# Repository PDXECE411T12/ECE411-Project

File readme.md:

# ECE 411 Team 12 
## RFID Smart Lock

### Fall 2020
### Authors: Miles Breslin, Miguel Higgins Moy, John Sharpe, Noah Page

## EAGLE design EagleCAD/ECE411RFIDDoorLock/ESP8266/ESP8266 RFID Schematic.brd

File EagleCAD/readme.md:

Schematic forked from Adafruit's wonderful ESP8266 Huzzah PCB

<https://github.com/PDXECE411T12/ECE411-RFID-Lock-Eagle>

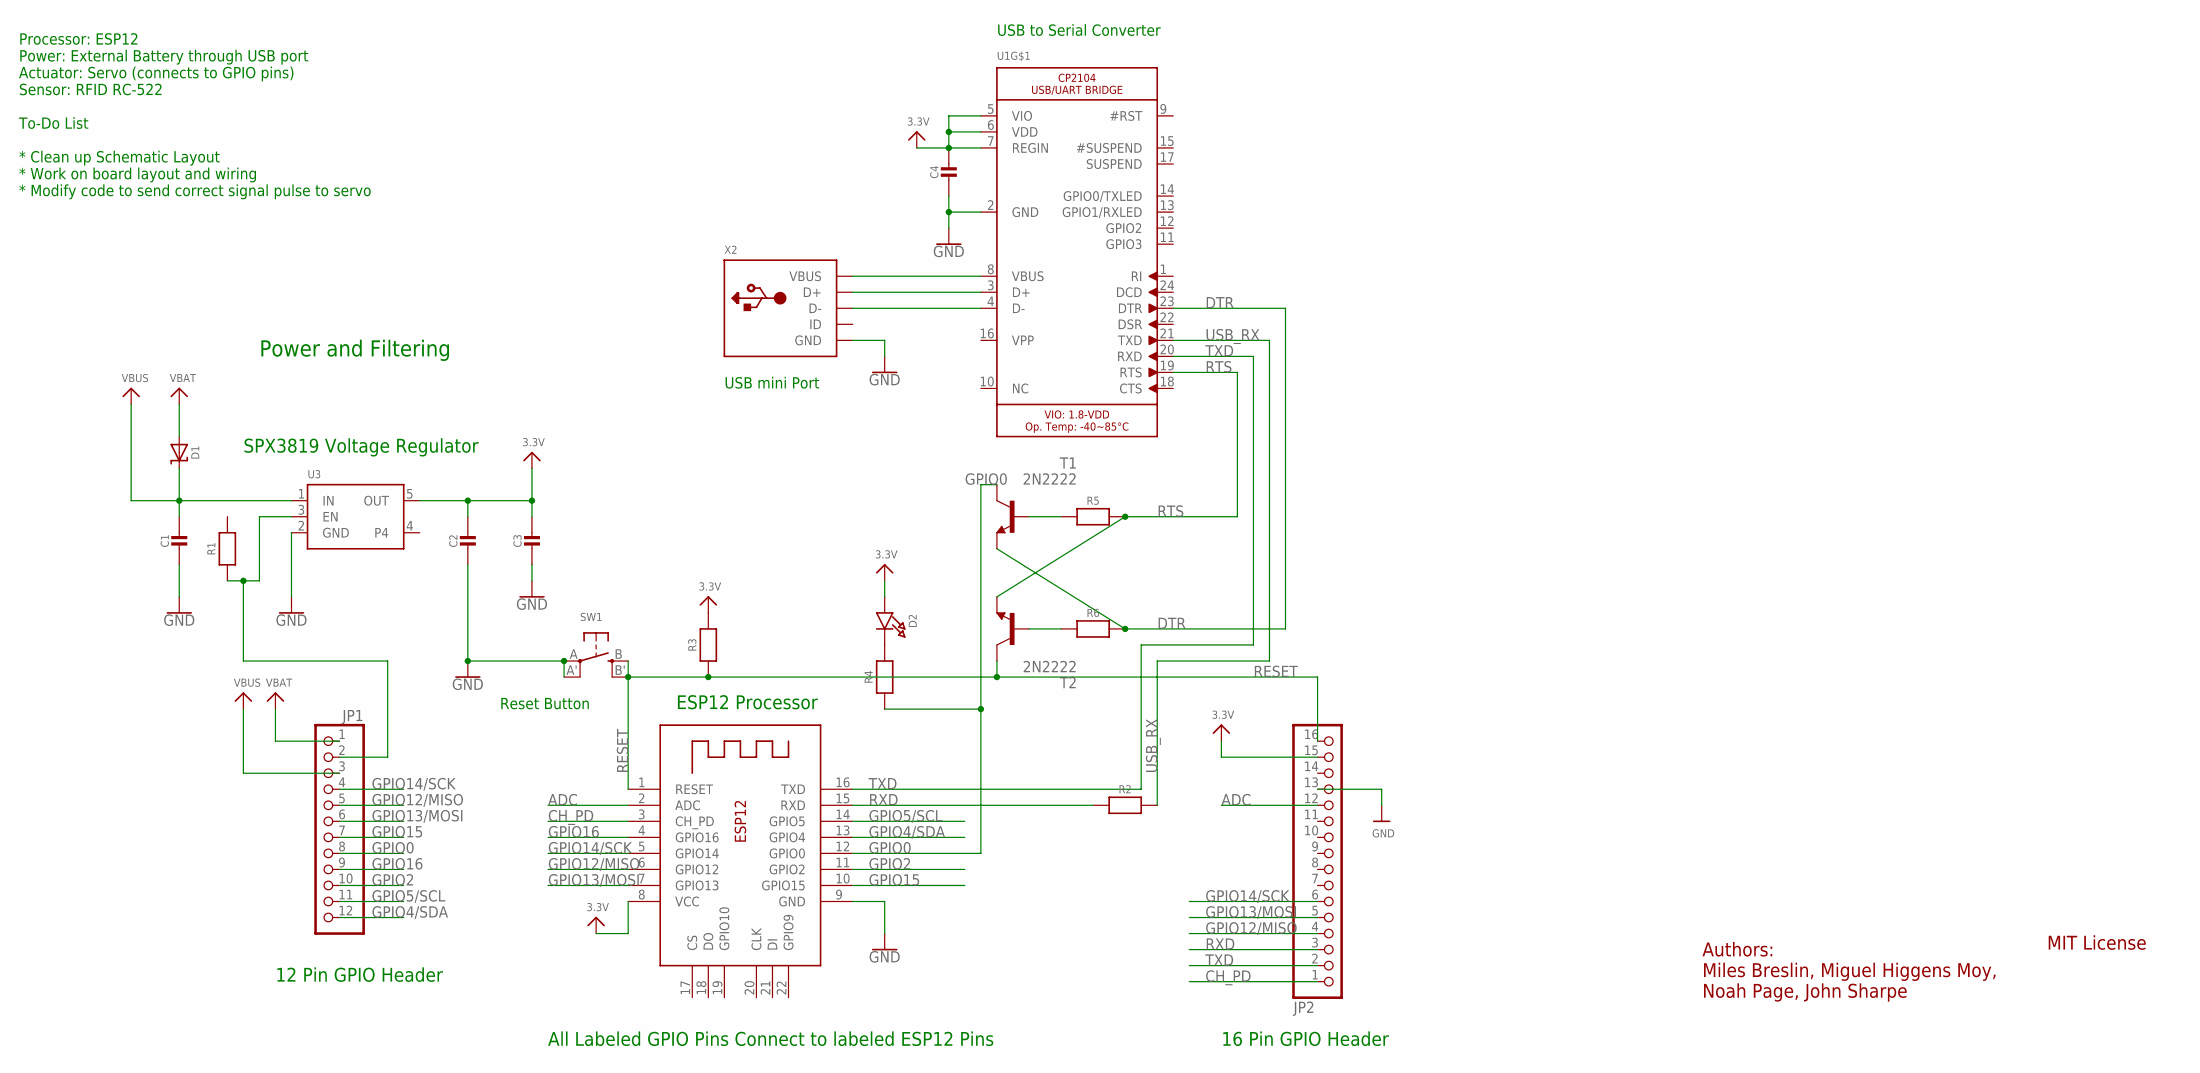
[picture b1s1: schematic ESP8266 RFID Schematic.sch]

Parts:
C1, C2, C3, C4: CAP_CERAMIC0603MINI; 0603-MINI
D1: DIODE-SCHOTTKYDO-1N4148; DO-1N4148
D2: LED0603; CHIPLED_0603
JP1: HEADER-1X12; 1X12_ROUND
JP2: HEADER-1X16; 1X16_OVAL
R1, R2, R3, R4, R5, R6: RESISTOR0603MINI; 0603-MINI
SW1: SWITCH_TACT_SMT; EVQ-Q2
T1, T2: 2N2222; TO92-EBC-OVAL
U1: CP2104; QFN24_4MM_SMSC
U3: VREG_SOT23-5; SOT23-5
X1: ESP-12E
X2: USBMINIB; USB-MINIB

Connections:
3.3V: C4.1, D2.A, JP2.15, R3.2, U1.5 (VIO), U1.6 (VDD), U1.7 (REGIN), X1.8 (VCC)
ADC: JP2.12, X1.2 (ADC)
CH_PD: JP2.1, X1.3 (CH_PD)
DTR: R6.2, T1.E, U1.23 (DTR)
GND: C1.2, C2.2, C3.2, C4.2, JP2.13, SW1.A, SW1.A' (P1), U1.2 (GND), U3.2 (GND), X1.9 (GND), X2.GND, X2.GND1 (GND), X2.GND2 (GND), X2.GND3 (GND), X2.GND4 (GND)
GPIO0: JP1.8, R4.1, T1.C, X1.12 (GPIO0)
GPIO2: JP1.10, X1.11 (GPIO2)
GPIO4/SDA: JP1.12, X1.13 (GPIO4)
GPIO5/SCL: JP1.11, X1.14 (GPIO5)
GPIO12/MISO: JP1.5, JP2.4, X1.6 (GPIO12)
GPIO13/MOSI: JP1.6, JP2.5, X1.7 (GPIO13)
GPIO14/SCK: JP1.4, JP2.6, X1.5 (GPIO14)
GPIO15: JP1.7, X1.10 (GPIO15)
GPIO16: JP1.9, X1.4 (GPIO16)
unnamed: JP1.2, R1.1, U3.3 (EN)
unnamed: U1.8 (VBUS), X2.VBUS
unnamed: U1.3 (D+), X2.D+
unnamed: U1.4 (D-), X2.D-
unnamed: D2.C, R4.2
unnamed: R5.1, T1.B
unnamed: R6.1, T2.B
OUT: C2.1, C3.1, U3.5 (OUT)
RESET: JP2.16, R3.1, SW1.B (S), SW1.B' (S1), T2.C, X1.1 (RESET)
RTS: R5.2, T2.E, U1.19 (RTS)
RXD: JP2.3, R2.1, X1.15 (RXD)
TP: U1.THERM (TP)
TXD: JP2.2, U1.20 (RXD), X1.16 (TXD)
USB_RX: R2.2, U1.21 (TXD)
VBAT: D1.A, JP1.1
VBUS: C1.1, D1.C, JP1.3, U3.1 (IN)

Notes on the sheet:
Authors: Miles Breslin, Miguel Higgens Moy, Noah Page, John Sharpe
MIT License
Power and Filtering
SPX3819 Voltage Regulator
12 Pin GPIO Header
16 Pin GPIO Header
All Labeled GPIO Pins Connect to labeled ESP12 Pins
ESP12 Processor
Reset Button
USB to Serial Converter
USB mini Port
Processor: ESP12 Power: External Battery through USB port Actuator: Servo (connects to GPIO pins) Sensor: RFID RC-522 To-Do List * Clean up Schematic Layout * Work on board layout and wiring * Modify code to send correct signal pulse to servo

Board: 2 copper layers, 21 parts (0 on the bottom side), 29 nets, no tracks yet.

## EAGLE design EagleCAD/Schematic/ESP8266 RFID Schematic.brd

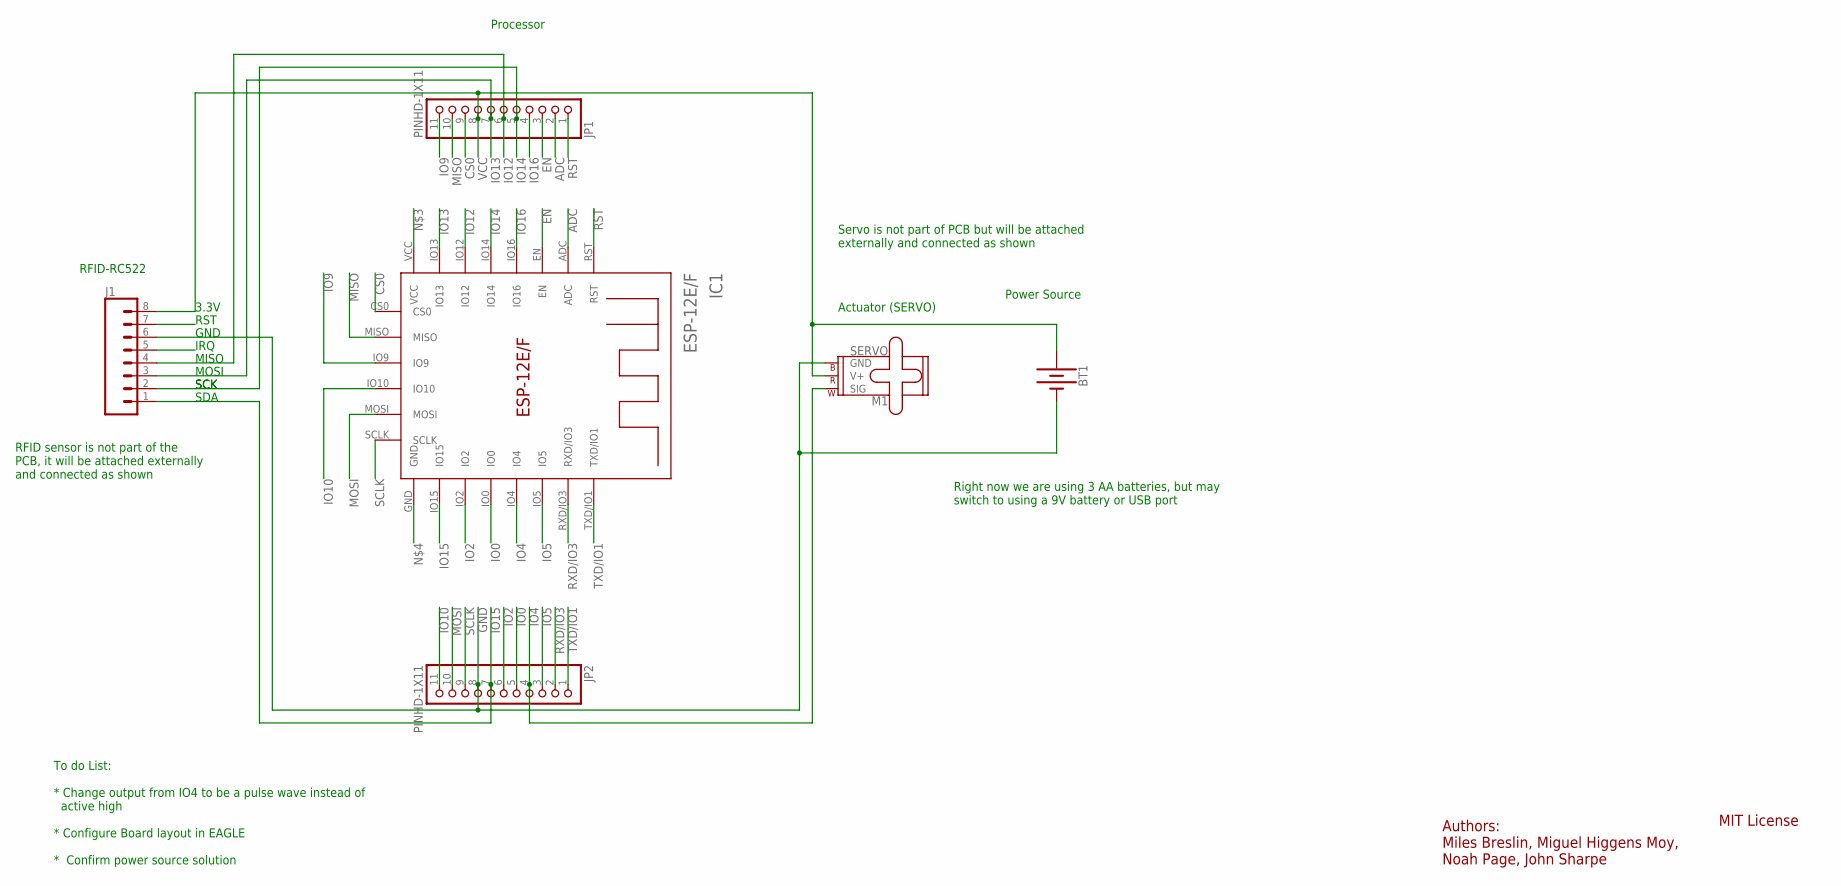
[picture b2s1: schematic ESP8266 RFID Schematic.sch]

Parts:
BT1: BATTERY-AA
IC1: ESP-12E/F; ESP-12E
J1: CONN_08"; 1X08
JP1, JP2: PINHD-1X11; 1X11
M1: SERVO; 1X03

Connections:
ADC: IC1.ADC, JP1.2
CS0: IC1.CS0, JP1.9
EN: IC1.EN, JP1.3
GND: BT1.GND@1 (-), J1.6, JP2.8, M1.3 (GND)
IO0: IC1.IO0, JP2.5
IO2: IC1.IO2, JP2.6
IO4: IC1.IO4, JP2.4, M1.1 (SIG)
IO5: IC1.IO5, JP2.3
IO9: IC1.IO9, JP1.11
IO10: IC1.IO10, JP2.11
IO12: J1.4, JP1.6
IO13: IC1.IO13, J1.3, JP1.7
IO14: J1.2, JP1.5
IO15: J1.1, JP2.7
IO16: IC1.IO16, JP1.4
IRQ: J1.5
MISO: IC1.MISO, JP1.10
MOSI: IC1.MOSI, JP2.10
RST: IC1.RST, J1.7, JP1.1
RXD/IO3: IC1.RXD/IO3, JP2.2
SCLK: IC1.SCLK, JP2.9
TXD/IO1: IC1.TXD/IO1, JP2.1
VCC: BT1.PWR@1 (+), J1.8, JP1.8, M1.2 (V+)

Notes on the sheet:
SCK
MOSI
MISO
3.3V
RST
GND
IRQ
RFID-RC522
SDA
Actuator (SERVO)
Power Source
Processor
RFID sensor is not part of the PCB, it will be attached externally and connected as shown
Servo is not part of PCB but will be attached externally and connected as shown
Right now we are using 3 AA batteries, but may switch to using a 9V battery or USB port
To do List: * Change output from IO4 to be a pulse wave instead of active high * Configure Board layout in EAGLE * Confirm power source solution
Authors: Miles Breslin, Miguel Higgens Moy, Noah Page, John Sharpe
MIT License

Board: 2 copper layers, 6 parts (0 on the bottom side), 22 nets, no tracks yet.

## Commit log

2020-10-08 Init
2020-10-08 Add copyright holders
2020-10-08 Add alternate project ideas
2020-10-15 Added folder
    Organizing and added Eagle empty project
2020-10-16 Added Homework 3 markdown
2020-10-16 Added Renders
2020-10-19 Shortened Executive Summary section, edited marketing detail at bottom of market analysis, added arduino IDE to Design Specification List
2020-10-20 Added a block diagram
2020-10-20 Title Update
2020-10-21 Update Homework 3.md
    added a few lines about price to Brief Market Analysis, and a line about how it works in Executive Summary
2020-10-21 Updated Render
2020-10-21 Updated Render for HW
2020-10-21 Added words to Progress So Far
2020-10-22 Updated IRL image
2020-10-22 HW3: Update some markdown formatting
2020-10-22 Added ESP12E Library - Use readme to add directory to your libraries - not entirely sure it will work for everyone
2020-11-01 Create Practicum Homework #4 Part 1: Breadboard Prototype
2020-11-01 Add files via upload
    Preliminary Schematic Design
2020-11-01 Update and rename Practicum Homework #4 Part 1: Breadboard Prototype to Practicum Homework #4 Breadboard Prototype and Preliminary Schematic
2020-11-02 Update Practicum Homework #4 Breadboard Prototype and Preliminary Schematic
2020-11-02 Update homework deliverables
2020-11-02 Init Eagle Schematic
2020-11-02 HW4: Fix markdown formatting
2020-11-02 HW4: Add Schematic
2020-11-07 rough draft of project schedule
2020-11-08 Rough Schematic layout of prototype board
2020-11-08 File clean up and organizing
2020-11-08 Placed derivative work under forked repo under the correct license
2020-11-08 Link change for Eagle files
2020-11-10 Updated project schedule, waiting for feedback from prof
2020-11-12 updated project schedule dependencies based on Mark's feedback
2020-11-12 images of project schedule
2020-11-12 Move project schedule in with the homework deliverables
2020-11-12 HW6: BoM
2020-11-12 updated schedule based on PHW7 Part 1 dates
2020-11-13 updated project schedule based on PHW7 11/12 lecture
2020-11-13 updated images
2020-11-17 Updated near final CAD and exported STLs
2020-11-18 Design review notes
2020-11-21 Create block diagrams
2020-11-29 3D CAD Final Edits
2020-12-07 updated PDS, HW3
2020-12-08 Added Homework 7.pdf
2020-12-09 Updated CAD Files
2020-12-09 Updated PDS document with 411 pract requirements
2020-12-09 Fixed block diagram image
2020-12-09 Total reorganization of files and file names
2020-12-09 img folder fixed for practicum
2020-12-09 Edited Needs statement, re-formated Requirements section.
2020-12-09 Fixed a typo in requirements section.
2020-12-09 Update BOM
2020-12-09 Fix markdown formatting
2020-12-09 Readme and link update
2020-12-09 Updated ProjectSchedule
2020-12-09 new project schedule img
2020-12-09 Added updated homework 5 and 6 pdfs
2020-12-09 Final presentation slides uploaded
    Links to photos/videos at last slide
2021-01-09 Added renders, clarified STL names, added pictures
2021-01-09 Revert "Final presentation slides uploaded"
    This reverts commit 290c40fa48d9f43e55ecc56ba741933645294e6f.
2021-01-09 Delete Homework 5 Detailed Design.md
    Revert "Final presentation slides uploaded"
    This reverts commit 290c40fa48d9f43e55ecc56ba741933645294e6f.
    Revert "Final presentation slides uploaded"
    This reverts commit 290c40fa48d9f43e55ecc56ba741933645294e6f.
2021-01-09 Firmware added
2021-01-09 Readme update

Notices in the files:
EagleCAD/ESP8266 RFID Schematic.sch:
LICENSE: MIT License
parts and their libraries:
SparkFun-PowerSymbols: Licensing: Creative Commons ShareAlike 4.0 International - https://creativecommons.org/licenses/by-sa/4.0
SparkFun-Aesthetics: Released under the Creative Commons Attribution Share-Alike 4.0 License
SparkFun-Aesthetics: https://creativecommons.org/licenses/by-sa/4.0
